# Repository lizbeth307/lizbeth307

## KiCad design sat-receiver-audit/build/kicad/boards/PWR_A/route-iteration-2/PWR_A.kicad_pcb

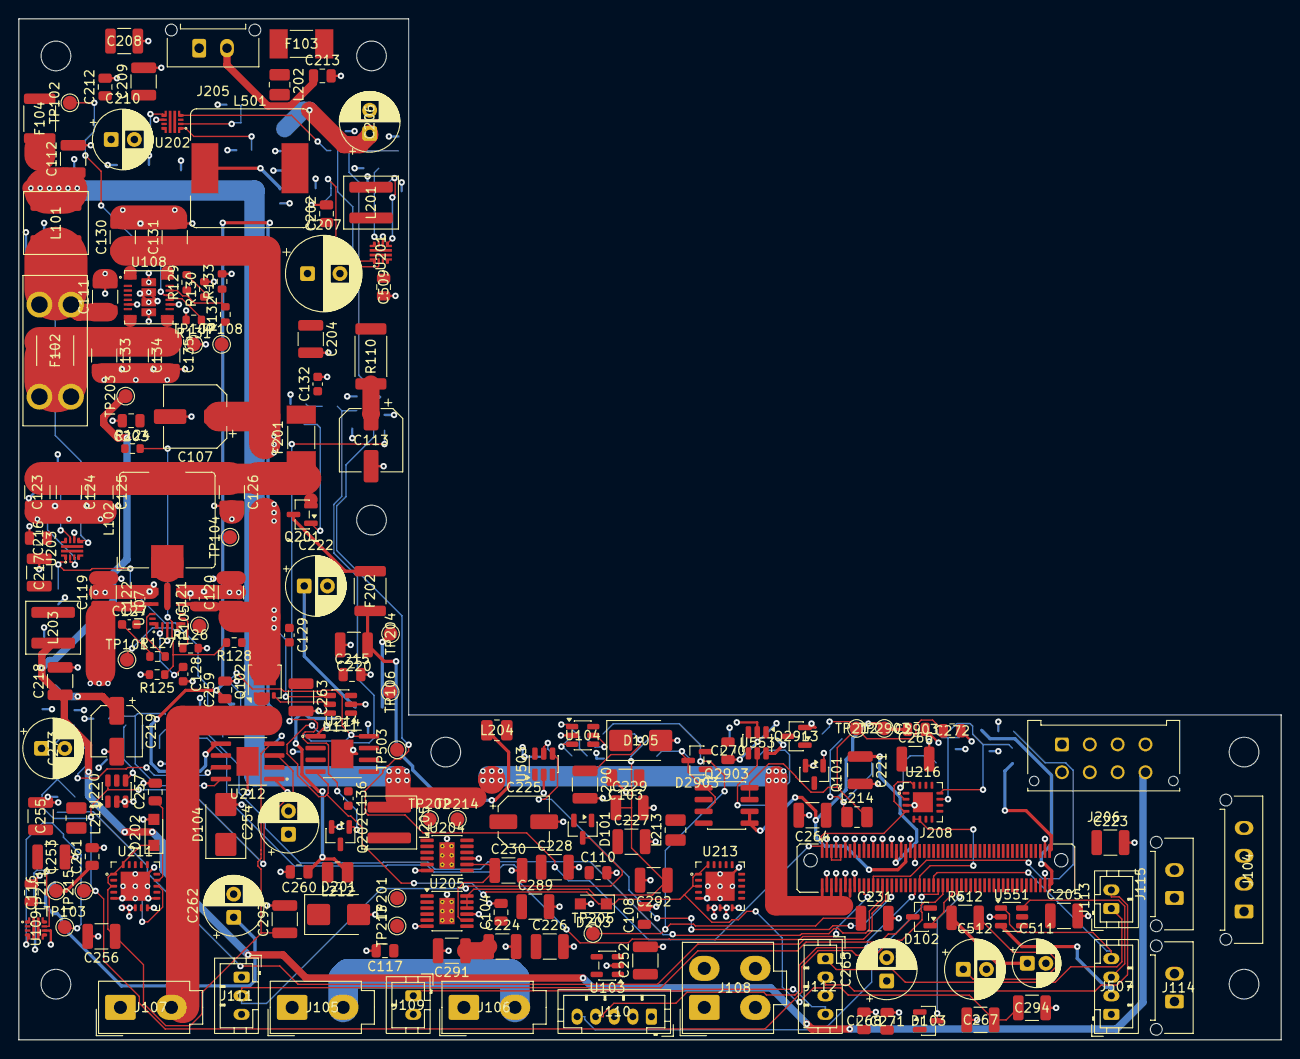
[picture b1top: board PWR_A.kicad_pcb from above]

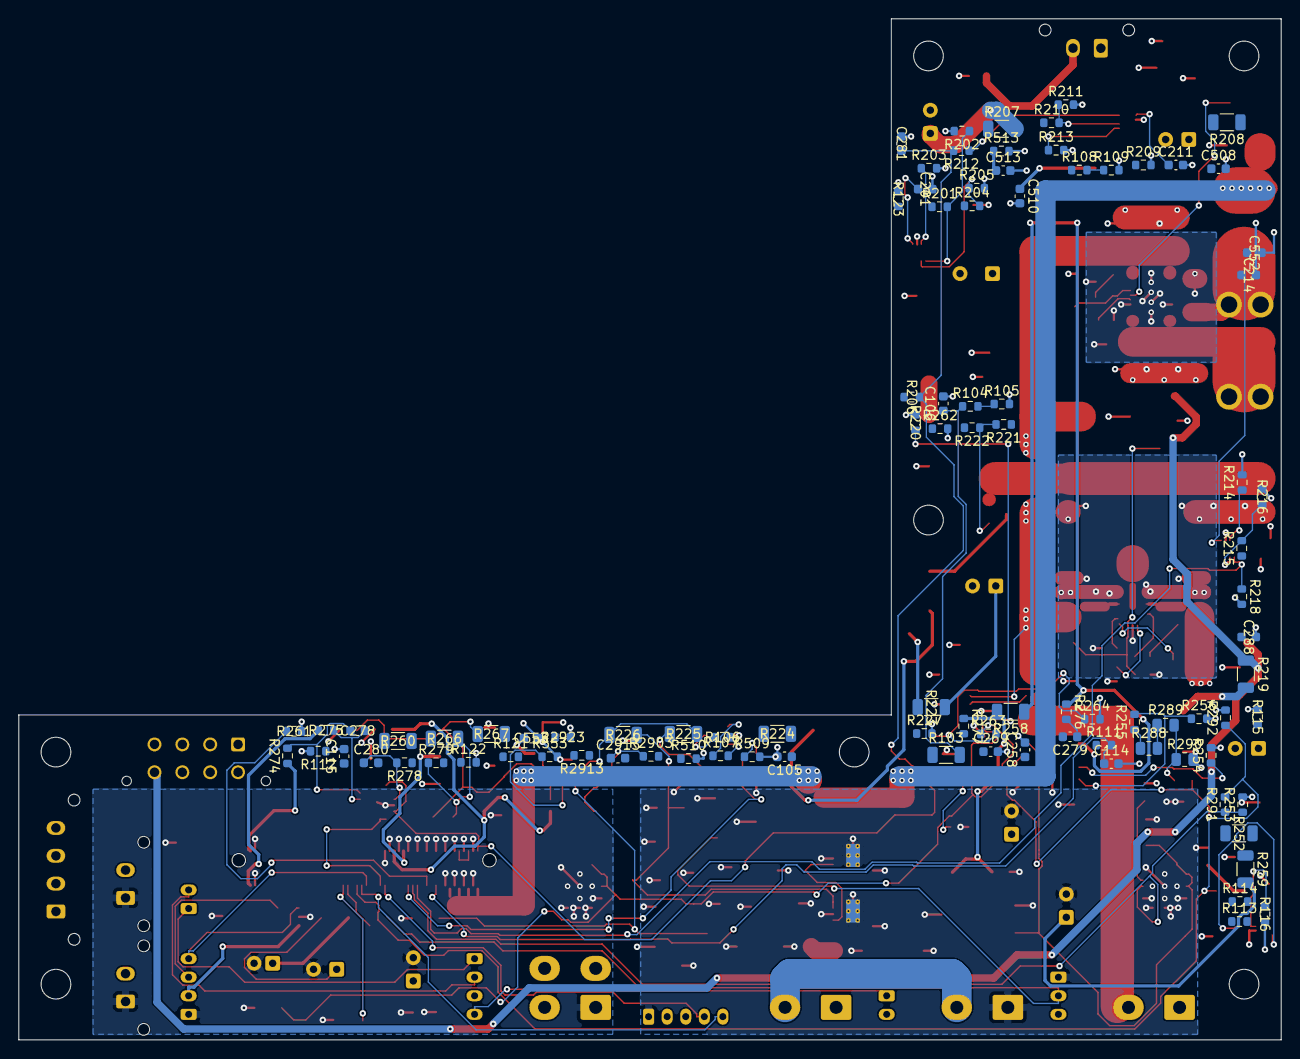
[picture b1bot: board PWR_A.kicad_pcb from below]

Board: 4 copper layers, 136.0 x 110.0 mm, 287 parts (94 on the bottom side), 148 nets.

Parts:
C103: 2.2µF50VX7R (effective≥1µF); C_1206_3216Metric
C104: 4.7µF10VX7R (effective≥2.2µF); C_0805_2012Metric
C105, C106: 100nF10VX7R; C_0603_1608Metric
C107: 100µF35VlowESR; CP_Elec_6.3x7.7
C108, C110, C116, C117: 1µF50VX7R; C_0805_2012Metric
C111, C112, C123, C124, C125, C126: 22µF50VX7R 1210 C3225X7R1H226M250AC; C_1210_3225Metric
C113: 16SVPC100M 100 µF 16 V ±20% OS-CON; CP_Elec_6.3x5.9
C114: 100nF10V; C_0603_1608Metric
C115: 3.3nF50VC0G; C_0603_1608Metric
C119, C120, C130, C131: 10µF50VX7R 1210; C_1210_3225Metric
C121, C122, C132: 100nF50VX7R; C_0603_1608Metric
C127: 100nF50VX7R CBOOT; C_0603_1608Metric
C128: 1µF16VX7R CVCC; C_0603_1608Metric
C129: 4.7pF50VC0G CFF; C_0603_1608Metric
C133, C134, C135: 47µF10VX7R 1210; C_1210_3225Metric
C136: 100nF50VX7R VCAP; C_0603_1608Metric
C201, C211, C214: 3.3nF 50V C0G C1608C0G1H332J080AA; C_0603_1608Metric
C202, C203, C212, C213, C215, C216, C257, C259, C260, C261, C268, C270, C271, C272, C2903: 1uF 50V X7R C2012X7R1H105K125AB; C_0805_2012Metric
C204, C205, C208, C209, C217, C218, C220, C221, C226, C228, C230, C252, C253, C255, C263, C264, C266, C289, C291: 10uF 50V X7R C3225X7R1H106K250AC; C_1210_3225Metric
C206, C210, C222, C254, C262, C265, C273: 47uF 50V EEUFR1H470; CP_Radial_D6.3mm_P2.50mm
C207: 220uF/25V UHE1E221MPD; CP_Radial_D8.0mm_P3.50mm
C219, C225: 47uF 10V 16SVPG47M; CP_Elec_5x4.5
C223, C224, C227, C229, C231, C256, C267, C290, C292, C293, C294: 22uF 50V X7R C3225X7R1H226M250AC; C_1210_3225Metric
C258: 47nF 50V X7R C1608X7R1H473K080AA; C_0603_1608Metric
C269, C278, C279, C280, C281, C288, C2913: 100nF 50V X7R C1608X7R1H104K080AA; C_0603_1608Metric
C508, C513, C552: 100nF X7R 10V; C_0603_1608Metric
C509: 4.7uF X7R 10V; C_0805_2012Metric
C510, C553: 1uF X7R 10V; C_0603_1608Metric
C511: EEU-FR1C101 100uF 16V; CP_Radial_D5.0mm_P2.00mm
C512: 220uF 16V low-ESR; CP_Radial_D6.3mm_P2.50mm
D101, D102, D103: BAT54,215; SOT-23
D104, D105: SMBJ17A-E3/52; D_SMB_KA
D201: SMBJ13A-E3/52; D_SMB_KA
D202, D203: PMEG4030ER; Nexperia_CFP3_SOD-123W
D2903: BZX84C10-7-F; SOT-23
F102: 4 A DC ≥32 V LAB5; Fuseholder_Blade_Mini_Keystone_3568
F103: 5A DC≥32V service SMD 0451005.MRL; Fuse_Littelfuse-NANO2-451_453
F104, F202: MF-MSMF075/24-2 0.75A; Fuse_1812_4532Metric
F201: Littelfuse 0451004.MRL 4A; Fuse_Littelfuse-NANO2-451_453
H1, H2, H3, H4, H5, H6, H7: NPTH_3.2mm
J104: X02P1-PWR: Molex Micro-Fit 3.0 4, верхній вхід, S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; Molex_Micro-Fit_3.0_43650-0415_1x04_P3.00mm_Vertical
J105: X05J1-PWR: Molex Mini-Fit Jr. 2×1, верхній вхід, 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; Molex_Mini-Fit_Jr_5566-02A_2x01_P4.20mm_Vertical
J106: X06J1-PWR: Molex Mini-Fit Jr. 2×1, верхній вхід, 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; Molex_Mini-Fit_Jr_5566-02A_2x01_P4.20mm_Vertical
J107: X07J1-PWR: Molex Mini-Fit Jr. 2×1, верхній вхід, 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; Molex_Mini-Fit_Jr_5566-02A_2x01_P4.20mm_Vertical
J108: X10J1-PWR: Molex Mini-Fit Jr. 2×2, верхній вхід, 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; Molex_Mini-Fit_Jr_5566-04A_2x02_P4.20mm_Vertical
J109: X05S1-PWR: JST PH 2, верхній вхід, S05; JST_PH_B2B-PH-K_1x02_P2.00mm_Vertical
J110: X06S1-PWR: JST PH 5, верхній вхід, S06; JST_PH_B5B-PH-K_1x05_P2.00mm_Vertical
J111: X07S1-PWR: JST PH 3, верхній вхід, S07; JST_PH_B3B-PH-K_1x03_P2.00mm_Vertical
J112: X10S1-PWR: JST PH 4, верхній вхід, S10; JST_PH_B4B-PH-K_1x04_P2.00mm_Vertical
J113: X11S1-PWR: JST PH 2, верхній вхід, S11; JST_PH_B2B-PH-K_1x02_P2.00mm_Vertical
J114: X11P1-PWR: Molex Micro-Fit 3.0 2, верхній вхід, S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; Molex_Micro-Fit_3.0_43650-0215_1x02_P3.00mm_Vertical
J115: X12P1-PWR: Molex Micro-Fit 3.0 2, верхній вхід, S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; Molex_Micro-Fit_3.0_43650-0215_1x02_P3.00mm_Vertical
J205: X19P1-PWR: Molex Micro-Fit 3.0 2, верхній вхід, S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; Molex_Micro-Fit_3.0_43650-0215_1x02_P3.00mm_Vertical
J206: SL2-PWR-MF: Molex Micro-Fit 3.0 2×4, верхній вхід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; Molex_Micro-Fit_3.0_43045-0812_2x04_P3.00mm_Vertical
J208: B2B-PWRA: Samtec LSHM-150 2×50, PWR-A верх, стик 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; Samtec_LSHM-150-xx.x-x-DV-N_2x50_P0.50mm_Vertical
J507: X32S1-PWR: JST PH 4, верхній вхід, S32; JST_PH_B4B-PH-K_1x04_P2.00mm_Vertical
L101: XAL6060-103MEC 10 µH ±20%; L_Coilcraft_XAL6060-XXX
L102: SRP1040VA-4R7M 4.7 µH ±20%; L_Bourns_SRP1038C_10.0x10.0mm
L201, L203, L205: 1uH XAL5030-102MEC; L_Coilcraft_XAL5030-XXX
L202, L204, L211, L212, L213, L214: 1uH SRP2510PA-1R0M; L_1008_2520Metric
L501: SRR1260-101M 100uH; L_Bourns_SRR1260
Q101: 2N7002,215; SOT-23
Q102: DMT6007LFG-7; Diodes_PowerDI3333-8
Q201: AO3407A; SOT-23
Q202, Q2913: 2N7002; SOT-23
Q2903: DMP6050SSD-13; SOIC-8_3.9x4.9mm_P1.27mm
R103: 3.30M0.1%25ppm; R_1206_3216Metric
R104: 332k0.1%25ppm; R_0603_1608Metric
R105: 4.02k0.1%25ppm TRIM; R_0603_1608Metric
R106, R111, R123, R124: 100k1%; R_0603_1608Metric
R107: 4.22M1%; R_0603_1608Metric
R108, R132: 1.00M1%; R_0603_1608Metric
R109: 115k1%; R_0603_1608Metric
R110: WSL2512R3300FEA 0.330 Ω 1%; R_2512_6332Metric
R112: 20.0k1%; R_0603_1608Metric
R113: 470k1%; R_0603_1608Metric
R114: 174k0.1%; R_0603_1608Metric
R115: 10.0k0.1%; R_0603_1608Metric
R116: 953Ω1%; R_0603_1608Metric
R121: 2.20k1%; R_0603_1608Metric
R122: 1.00k1%; R_0603_1608Metric
R125: 9.09k0.1%; R_0603_1608Metric
R126, R131: 14.3k1%; R_0603_1608Metric
R127: 100Ω1% RBOOT; R_0603_1608Metric
R128: 1.00k1% RFF; R_0603_1608Metric
R129: 40.2k1%; R_0603_1608Metric
R130: 10.0k1%; R_0603_1608Metric
R133: 147k1%; R_0603_1608Metric
R201, R213, R218, R220, R253, R261, R292, R2903: 100k 1%; R_0603_1608Metric
R202: 13.0k 1% 100ppm; R_0603_1608Metric
R203: 825R 1%; R_0603_1608Metric
R204, R210: 102k 0.1%; R_0603_1608Metric
R205, R211, R216: 10.0k 0.1%; R_0603_1608Metric
R206, R212, R221, R222, R2923: 10.0k 1%; R_0603_1608Metric
R207, R208, R223, R252, R259, R260, R267: 0.22R 1% 0.25W; R_1206_3216Metric
R209: 1.96k 1%; R_0603_1608Metric
R214: 1.65k 1%; R_0603_1608Metric
R215: 19.6k 0.1%; R_0603_1608Metric
R219, R224: 0.15R 1% 0.25W; R_1206_3216Metric
R225, R226: 20mR 1% 0.25W; R_1206_3216Metric
R227: 21.5k 0.1% 25ppm; R_0603_1608Metric
R254: 2.05k 1%; R_0603_1608Metric
R255: 110k 0.5%; R_0603_1608Metric
R256: 10.0k 0.5%; R_0603_1608Metric
R258: 0.100R 0.1% 0.25W Kelvin; R_1206_3216Metric
R262: 7.15k 1% 100ppm; R_0603_1608Metric
R263: OVLO TBD (start 102k 0.1%); R_0603_1608Metric
R264: OVLO TBD (start 9.09k 0.1%); R_0603_1608Metric
R266: 0.200R 0.1% 0.25W Kelvin; R_1206_3216Metric
R274, R275, R276, R277, R278, R279: 10.0R 1%; R_0603_1608Metric
R288: TNPW0805332KBYEA 332k 0.1%10ppm; R_0805_2012Metric
R289: TNPW08052K00BYEA 2.00k 0.1%10ppm; R_0805_2012Metric
R290: TNPW080510K0BYEA 10.0k 0.1%10ppm; R_0805_2012Metric
R291: 4.70k 1%; R_0603_1608Metric
R509: RILIM TBD (start 28.7k 1%); R_0603_1608Metric
R510: 100k; R_0603_1608Metric
R512: 1Ohm 0.5W; R_1210_3225Metric
R513: 10k; R_0603_1608Metric
R553: RILIM TBD (start 88.7k 1%); R_0603_1608Metric
R2913: 22k 1%; R_0603_1608Metric
TP101: PG_SYS12резерв; TestPoint_Pad_D1.5mm
TP102: PG_LAB5резерв; TestPoint_Pad_D1.5mm
TP103: PD_FLT service; TestPoint_Pad_D1.5mm
TP104: ВузолN; TestPoint_Pad_D1.5mm
TP105: ВузолSW; TestPoint_Pad_D1.5mm
TP106: AON3V3; TestPoint_Pad_D1.5mm
TP107: Protectedground; TestPoint_Pad_D1.5mm
TP108: UV_OFF; TestPoint_Pad_D1.5mm
TP201: J21; TestPoint_Pad_D1.5mm
TP202: DISP12; TestPoint_Pad_D1.5mm
TP203: LIME3V3; TestPoint_Pad_D1.5mm
TP204: AUX12; TestPoint_Pad_D1.5mm
TP205: LNA4V5; TestPoint_Pad_D1.5mm
TP211: LNB13V2; TestPoint_Pad_D1.5mm
TP212: BONI13V8; TestPoint_Pad_D1.5mm
TP213: E2_FAULT_J21; TestPoint_Pad_D1.5mm
TP214: E2_FAULT_DISP; TestPoint_Pad_D1.5mm
TP215: OVP_LNB_N; TestPoint_Pad_D1.5mm
TP503: IMU 5V switch FAULT_N test point; TestPoint_Pad_D1.5mm
TP2903: BONI13V8_PORT; TestPoint_Pad_D1.5mm
U103: TPS70933DBVR; SOT-23-5
U104: MCP65R41T-1202E/CHY; SOT-23-6
U107: LM61460AANRJRR; TI_RJR0014A_VQFN-HR-14_4x3.5mm
U108: TPSM63606RDLR — LAB5 default; TI_RDL0020A_B3QFN-20_5x5.5mm
U109: TPS259470ARPWR USB-C; TI_RPW0010A_VQFN-HR-10_2x2mm_P0.5mm
U111: LM74700QDBVRQ1; SOT-23-6
U201, U202, U203: TPS259470ARPWR; TI_RPW0010A_VQFN-HR-10_2x2mm_P0.5mm
U204, U205: LT3045EMSE#PBF; MSOP-12-1EP_3x4.039mm_P0.65mm_EP1.651x2.845mm_ThermalVias
U211, U213: TPS7A4701RGWT; TI_RGW0020A_VQFN-20-1EP_5x5mm_P0.65mm_EP3.15x3.15mm
U212, U214: TPS259630DDAR; TI_DDA0008_HSOP-8-1EP_3.9x4.9mm_P1.27mm_EP2.4x3.1mm
U216: INA3221AIRGVR; TI_RGV0016A_VQFN-16-1EP_4x4mm_P0.65mm_EP2.16x2.16mm
U220: TPS3701DDCR; TSOT-23-6
U503: TPS2553DBVR-1; SOT-23-6
U551: TPD4E1U06DBVR; SOT-23-6
U553: TPS2553DBVR; SOT-23-6

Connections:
3V3_Q6A: C281.1, J208.1, R206.2, R212.2, U216.4, U216.16
AON3V3: C104.1, C105.1, J110.2, TP106.1, U103.5, U104.6
AUX12: C221.1, J208.33, L204.2, R223.1, TP204.1
AUX12_DAMP: C222.1, R223.2
BONI13V8: C272.1, J208.25, L214.2, Q2903.7, Q2903.8, R267.1, R2923.1, TP212.1
BONI13V8_DAMP: C273.1, R267.2
BONI13V8_PORT: C2903.1, J208.37, Q2903.5, Q2903.6, TP2903.1
CHG_INHIBIT: J208.18, R122.1
DISP12: C213.1, J205.2, TP202.1, U202.6
E1_BAT_ADC: C114.1, J208.20, R111.2, R112.1
E1_CHG_CC1: J112.1, J113.1
E1_CHG_CC2: J112.2, J113.2
E1_CHG_GATE: Q101.1, R122.2, R123.1
E1_CHG_INHIBIT_LOW: J112.3, Q101.3, R121.2
E1_CHG_NTC: J109.1, J112.4, R121.1
E1_CONV_IN: C107.1, C119.1, C120.1, C121.1, C122.1, C130.1, C131.1, C132.1, Q102.5, R108.1, R132.1, U107.8, U107.12, U108.1, U108.16, U111.4
E1_EN_LAB5: R132.2, R133.1, U108.14
E1_EN_SYS12: R108.2, R109.1, U107.7
E1_LAB5_DAMP: C113.1, R110.2
E1_LAB5_FB: R129.2, R130.1, U108.10
E1_LAB5_FUSED: C111.1, F102.2, L101.1
E1_LAB5_RAW: C133.1, C134.1, C135.1, F102.1, R129.1, U108.5, U108.8, U108.9
E1_LAB5_RT: R131.1, U108.12
E1_MASTER_OFF: D101.3, D102.3, J111.2
E1_N: C103.1, D104.K, F103.1, J106.1, J107.1, J108.2, R103.1, TP104.1, U103.1
E1_PD_DVDT: C115.1, U109.7
E1_PD_EN: R113.2, U109.1
E1_PD_FLT: TP103.1, U109.4
E1_PD_ILM: R116.1, U109.9
E1_PD_OVLO: R114.2, R115.1, U109.2
E1_PG_LAB5: TP102.1, U108.13
E1_PG_SYS12: TP101.1, U107.5
E1_RPP_GATE: Q102.4, U111.5
E1_RPP_VCAP: C136.1, U111.1
E1_SERVICE_P: F103.2, J115.2
E1_SHUNT_P: J105.2, J106.2
E1_SW: C108.1, C110.1, C136.2, C252.1, C263.1, C288.1, D105.K, J107.2, L211.1, L213.1, Q102.1, Q102.2, Q102.3, R111.1, TP105.1, U111.3, U111.6, U220.5
E1_SWITCH_A: D103.1, J111.3
E1_SYS12_CBOOT: C127.1, R127.1, U107.14
E1_SYS12_FB: R124.2, R125.1, R128.2, U107.4
E1_SYS12_FF: C129.2, R128.1
E1_SYS12_RBOOT: R127.2, U107.13
E1_SYS12_RT: R126.1, U107.6
E1_SYS12_SW: C127.2, L102.1, U107.10
E1_SYS12_VCC: C128.1, U107.2
E1_USB_PD_RAW: C116.1, J114.2, R113.1, R114.1, U109.5
E1_USB_PD_SAFE: C117.1, J108.3, U109.6
E1_UV_OFF: D101.1, R107.1, TP108.1, U104.1
E1_UV_REF: R106.1, U104.5
E1_UV_REFH: R106.2, R107.2, U104.3
E1_UV_SENSE: C106.1, R103.2, R104.1, U104.4
E1_UV_TRIM: R104.2, R105.1
E2_AUX_GATE: Q201.1, R221.2, R222.1
E2_AUX_GSINK: Q202.3, R222.2
E2_AUX_PTC: C220.1, F202.2, L204.1
E2_AUX_SWITCHED: F202.1, Q201.3
E2_BLKB_G: C2913.2, D2903.1, Q2903.2, Q2903.4, R2903.2, R2913.1
E2_BLKB_S: C2913.1, D2903.3, Q2903.1, Q2903.3, R2903.1
E2_BLKB_SINK: Q2913.3, R2913.2
E2_BONI_DVDT: C269.1, U214.2
E2_BONI_EF: C270.1, R266.1, R278.1, U214.5
E2_BONI_ILM: R262.1, U214.7
E2_BONI_IN: C264.1, C266.1, L213.2, R260.1, U213.15, U213.16
E2_BONI_IN_DAMP: C265.1, R260.2
E2_BONI_LDO: C267.1, C294.1, D203.1, R263.1, U213.1, U213.3, U213.20, U214.4
E2_BONI_MON: C271.1, L214.1, R266.2, R279.1
E2_BONI_NR: C268.1, U213.14
E2_BONI_OV: R263.2, R264.1, U214.8
E2_DISP_IN: C209.1, C212.1, L202.2, R208.1, R210.1, U202.5
E2_DISP_IN_DAMP: C210.1, R208.2
E2_FAULT_DISP: R212.1, TP214.1, U202.4
E2_FAULT_J21: R206.1, TP213.1, U201.4
E2_J21_EF: C203.1, C204.1, L201.1, U201.6
E2_J21_EN: R201.2, R202.1, U201.1
E2_J21_FUSED: C202.1, F201.2, R201.1, R204.1, U201.5
E2_LIME_EF: C216.1, C217.1, L203.1, U203.6
E2_LNA4_SHUNT: J208.100, R275.1
E2_LNA4_SW: J208.99, R274.1
E2_LNA_IN: C224.1, C226.1, C228.1, C289.1, C291.1, L205.2, R224.1, U204.1, U204.2, U204.3, U204.4, U204.7, U205.1, U205.2, U205.3, U205.4, U205.7
E2_LNA_IN_DAMP: C225.1, R224.2
E2_LNA_SET: C230.1, R227.1, U204.8, U205.8
E2_LNB_DVDT: C258.1, U212.2
E2_LNB_EF: C259.1, R258.1, R276.1, U212.5
E2_LNB_ILM: R254.1, U212.7
E2_LNB_IN: C253.1, C255.1, L211.2, R252.1, U211.15, U211.16
E2_LNB_IN_DAMP: C254.1, R252.2
E2_LNB_LDO: C256.1, C293.1, D202.1, R255.1, R288.1, U211.1, U211.3, U211.20, U212.4
E2_LNB_MON: C260.1, L212.1, R258.2, R277.1
E2_LNB_NR: C257.1, U211.14
E2_LNB_OV: R255.2, R256.1, U212.8
E2_LNB_OV_DIV_MID: R288.2, R289.1
E2_LNB_PRECISE_SENSE: R289.2, R290.1, U220.4
E2_LT_OUT1: C227.1, C290.1, R225.1, U204.10, U204.11, U204.12
E2_LT_OUT2: C229.1, C292.1, R226.1, U205.10, U205.11, U205.12
E2_U201_DVDT: C201.1, U201.7
E2_U201_ILM: R203.1, U201.9
E2_U201_OV: R204.2, R205.1, U201.2
E2_U202_DVDT: C211.1, U202.7
E2_U202_ILM: R209.1, U202.9
E2_U202_OV: R210.2, R211.1, U202.2
E2_U203_DVDT: C214.1, U203.7
E2_U203_ILM: R214.1, U203.9
E2_U203_OV: R215.2, R216.1, U203.2
E2_U216_IM1: C278.2, R275.2, U216.11
E2_U216_IM2: C279.2, R277.2, U216.14
E2_U216_IM3: C280.2, R279.2, U216.1
E2_U216_IP1: C278.1, R274.2, U216.12
E2_U216_IP2: C279.1, R276.2, U216.15
E2_U216_IP3: C280.1, R278.2, U216.2
E5_HFP_DAMP: C512.1, R512.2
E5_IMU5V: C553.1, J507.2, U551.3, U553.6
E5_IMU_FAULT: TP503.1, U553.4
E5_U503_ILIM: R509.1, U503.5
E5_U553_ILIM: R553.1, U553.5
E5_VBUS_HFP_SW: C510.1, L501.1, U503.6
EN_AUX12: J208.22, Q202.1, R220.1
EN_BONI: J208.24, Q2913.1, R261.1, U213.13, U214.3
EN_HFP: J208.26, R510.1, U503.3
EN_LIME3V3: J208.28, R218.1, U203.1
EN_LNB: J208.30, R253.1, R291.1, U211.13
FAULT_HFP: J208.32, U503.4
FLT_BONI: J208.34, U214.6
FLT_LIME3V3: J208.36, U203.4
FLT_LNB: J208.38, U212.6
GND: C103.2, C104.2, C105.2, C106.2, C107.2, C108.2, C110.2, C111.2, C112.2, C113.2, C114.2, C115.2, C116.2, C117.2, C119.2, C120.2, C121.2, C122.2, C123.2, C124.2, C125.2, C126.2, C128.2, C130.2, C131.2, C132.2, C133.2, C134.2, C135.2, C201.2, C202.2, C203.2, C204.2, C205.2, C206.2, C207.2, C208.2, C209.2, C210.2, C211.2, C212.2, C213.2, C214.2, C215.2, C216.2, C217.2, C218.2, C219.2, C220.2, C221.2, C222.2, C223.2, C224.2, C225.2, C226.2, C227.2, C228.2, C229.2, C230.2, C231.2, C252.2, C253.2, C254.2, C255.2, C256.2, C257.2, C258.2, C259.2, C260.2, C261.2, C262.2, C263.2, C264.2, C265.2, C266.2, C267.2, C268.2, C269.2, C270.2, C271.2, C272.2, C273.2, C281.2, C288.2, C289.2, C290.2, C291.2, C292.2, C293.2, C294.2, C508.2, C509.2, C510.2, C511.2, C512.2, C513.2, C552.2, C553.2, C2903.2, D104.A, D105.A, D201.A, D202.2, D203.2, J104.1, J104.2, J105.1, J108.1, J110.1, J111.1, J114.1, J115.1, J205.1, J206.1, J206.3, J206.5, J206.7, J208.3, J208.4, J208.7, J208.8, J208.11, J208.12, J208.15, J208.16, J208.19, J208.23, J208.27, J208.31, J208.35, J208.39, J208.41, J208.97, J208.98, J507.1, Q101.2, Q202.2, Q2913.2, R105.2, R109.2, R112.2, R115.2, R116.2, R123.2, R125.2, R126.2, R130.2, R131.2, R133.2, R202.2, R203.2, R205.2, R209.2, R211.2, R213.2, R214.2, R216.2, R218.2, R220.2, R227.2, R253.2, R254.2, R256.2, R261.2, R262.2, R264.2, R290.2, R292.2, R509.2, R510.2, R513.2, R553.2, R2923.2, TP107.1, U103.2, U104.2, U107.3, U107.9, U107.11, U108.6, U108.11, U108.17, U108.18, U108.19, U108.20, U109.8, U111.2, U201.8, U202.8, U203.8, U204.6, U204.9, U204.13, U205.6, U205.9, U205.13, U211.5, U211.6, U211.7, U211.8, U211.10, U211.11, U211.EP, U212.1, U212.EP, U213.5, U213.6, U213.7, U213.8, U213.9, U213.10, U213.EP, U214.1, U214.EP, U216.3, U216.EP, U220.2, U220.3, U503.2, U551.2, U553.2
I2C0_SCL: J110.3, J208.40
I2C0_SDA: J110.4, J208.42
I2C2_SCL: J208.44, U216.5, U216.6
I2C2_SDA: J208.46, U216.7
IMU_RX: J208.48, J507.3, U551.6
IMU_TX: J208.50, J507.4, U551.1
INA228_ALERT: J110.5, J208.52
J21: C205.1, C207.1, D201.K, J206.4, L201.2, R207.1, TP201.1
J21_DAMP: C206.1, R207.2
LAB5: C112.1, C223.1, C508.1, C509.1, C552.1, F104.1, J104.3, J104.4, J206.2, J208.2, J208.6, J208.10, J208.14, L101.2, L205.1, R110.1, U503.1, U553.1, U553.3
LAB5_RLY: F104.2, J208.17, J208.21
LIME3V3: C218.1, J206.8, L203.2, R219.1, TP203.1
LIME3V3_DAMP: C219.1, R219.2
LNA4V5: C231.1, J208.5, J208.9, R225.2, R226.2, TP205.1
LNB13V2: C261.1, J208.29, L212.2, R259.1, TP211.1
LNB13V2_DAMP: C262.1, R259.2
OVP_LNB_N: J208.54, R291.2, R292.1, TP215.1, U212.3, U220.6
PICO_DISP_EN: J208.56, R213.1, U202.1
PICO_OFF: D102.1, J208.58
PWR_BUTTON: D103.3, J208.60
SYS12: C123.1, C124.1, C125.1, C126.1, C129.1, C208.1, F201.1, L102.2, L202.1, Q201.2, R124.1, R221.1, U107.1
VBUS_HFP: C511.1, C513.1, J208.13, L501.2, R512.1, R513.1
VCC_3V3_MKEY: C215.1, J206.6, R215.1, U203.5
